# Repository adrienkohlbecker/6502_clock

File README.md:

# 6502 clock

## Board

## Schematic

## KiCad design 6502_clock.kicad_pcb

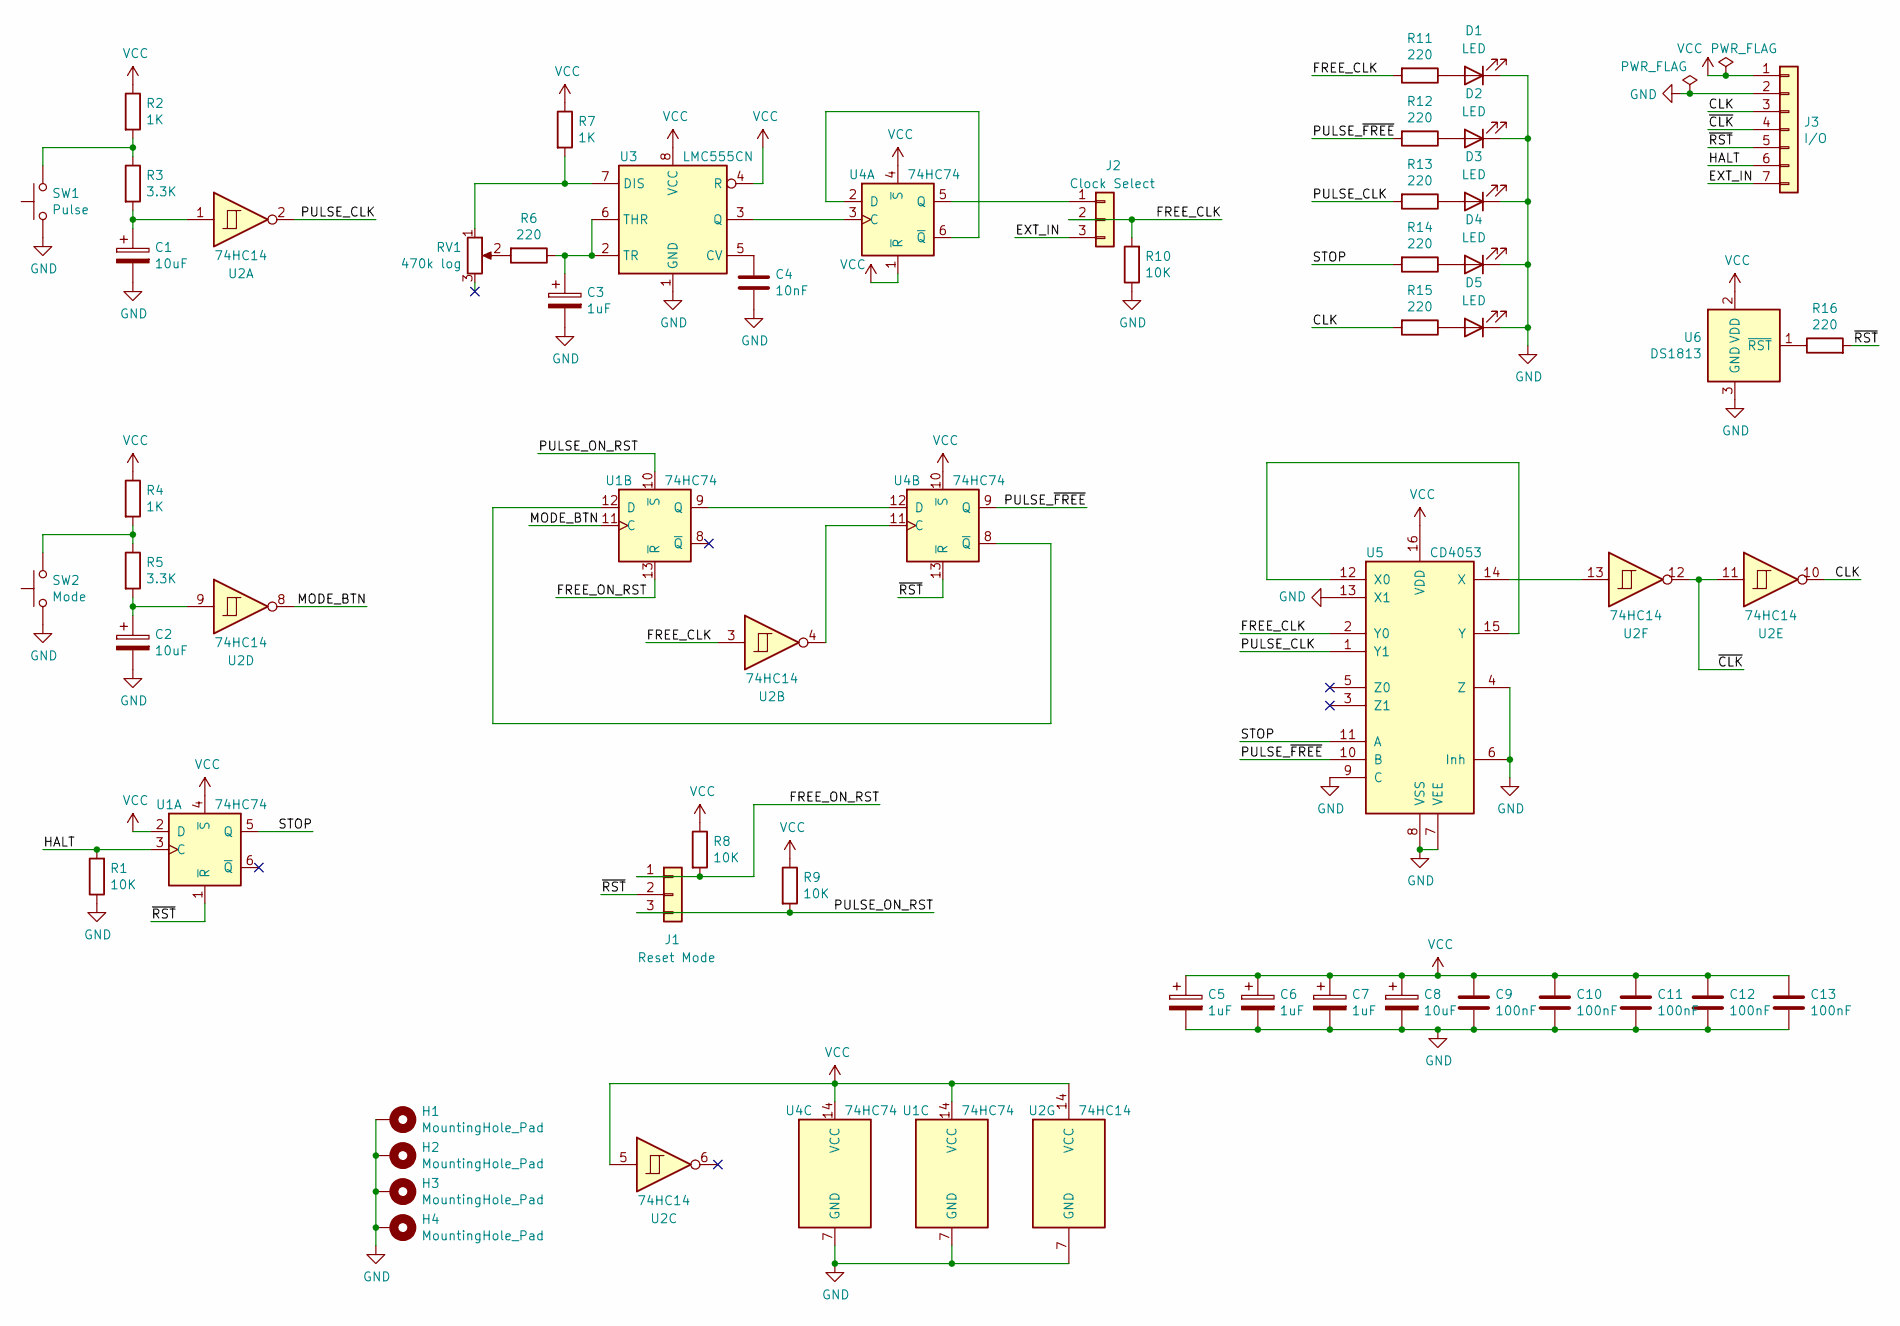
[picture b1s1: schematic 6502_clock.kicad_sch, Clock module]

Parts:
C1, C2, C8: 10uF; CP_Radial_D4.0mm_P2.00mm
C3, C5, C6, C7: 1uF; CP_Radial_D4.0mm_P2.00mm
C4: 10nF; C_Disc_D6.0mm_W2.5mm_P5.00mm
C9, C10, C11, C12, C13: 100nF; C_Disc_D5.0mm_W2.5mm_P2.50mm
D1, D2, D3, D4, D5: LED; LED_D3.0mm
H1, H2, H3, H4: MountingHole_Pad; MountingHole_3.2mm_M3_Pad
J1: Reset Mode; PinSocket_1x03_P2.54mm_Vertical
J2: Clock Select; PinSocket_1x03_P2.54mm_Vertical
J3: I/O; PinSocket_1x07_P2.54mm_Vertical
R1, R8, R9, R10: 10K; R_Axial_DIN0207_L6.3mm_D2.5mm_P7.62mm_Horizontal
R2, R4, R7: 1K; R_Axial_DIN0207_L6.3mm_D2.5mm_P7.62mm_Horizontal
R3, R5: 3.3K; R_Axial_DIN0207_L6.3mm_D2.5mm_P7.62mm_Horizontal
R6, R11, R12, R13, R14, R15, R16: 220; R_Axial_DIN0207_L6.3mm_D2.5mm_P7.62mm_Horizontal
RV1: 470k log; Potentiometer_P160KN-0QC15C500K
SW1: Pulse; SW_PUSH_6mm
SW2: Mode; SW_PUSH_6mm
U1, U4: 74HC74; DIP-14_W7.62mm
U2: 74HC14; DIP-14_W7.62mm
U3: LMC555CN; DIP-8_W7.62mm
U5: CD4053; DIP-16_W7.62mm
U6: DS1813; TO-92_Inline

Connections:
CLK: J3.3, R15.2, U2.10
EXT_IN: J2.3, J3.7
FREE_CLK: J2.2, R10.2, R11.2, U2.3, U5.2 (Y0)
FREE_ON_RST: J1.1, R8.2, U1.13 (~R)
GND: C1.2, C2.2, C3.2, C4.1, C5.2, C6.2, C7.2, C8.2, C9.1, C10.1, C11.1, C12.1, C13.1, D1.1 (K), D2.1 (K), D3.1 (K), D4.1 (K), D5.1 (K), H1.1, H2.1, H3.1, H4.1, J3.2, R1.1, R10.1, SW1.1, SW2.1, U1.7 (GND), U2.7 (GND), U3.1 (GND), U4.7 (GND), U5.4 (Z), U5.6 (Inh), U5.7 (VEE), U5.8 (VSS), U5.9 (C), U5.13 (X1), U6.3 (GND)
HALT: J3.6, R1.2, U1.3 (C)
MODE_BTN: U1.11 (C), U2.8
unnamed: C1.1, R3.2, U2.1
unnamed: C2.1, R5.2, U2.9
unnamed: C3.1, R6.1, U3.2 (TR), U3.6 (THR)
unnamed: C4.2, U3.5 (CV)
unnamed: D1.2 (A), R11.1
unnamed: D2.2 (A), R12.1
unnamed: D3.2 (A), R13.1
unnamed: D4.2 (A), R14.1
unnamed: D5.2 (A), R15.1
unnamed: J2.1, U4.5 (Q)
unnamed: R2.2, R3.1, SW1.2
unnamed: R4.2, R5.1, SW2.2
unnamed: R6.2, RV1.2
unnamed: R7.2, RV1.1, U3.7 (DIS)
unnamed: R16.1, U6.1 (~RST)
unnamed: U1.9 (Q), U4.12 (D)
unnamed: U1.12 (D), U4.8 (~Q)
unnamed: U2.4, U4.11 (C)
unnamed: U2.13, U5.14 (X)
unnamed: U3.3 (Q), U4.3 (C)
unnamed: U4.2 (D), U4.6 (~Q)
unnamed: U5.12 (X0), U5.15 (Y)
PULSE_CLK: R13.2, U2.2, U5.1 (Y1)
PULSE_ON_RST: J1.3, R9.2, U1.10 (~S)
PULSE_~FREE: R12.2, U4.9 (Q), U5.10 (B)
STOP: R14.2, U1.5 (Q), U5.11 (A)
VCC: C5.1, C6.1, C7.1, C8.1, C9.2, C10.2, C11.2, C12.2, C13.2, J3.1, R2.1, R4.1, R7.1, R8.1, R9.1, U1.2 (D), U1.4 (~S), U1.14 (VCC), U2.5, U2.14 (VCC), U3.4 (R), U3.8 (VCC), U4.1 (~R), U4.4 (~S), U4.10 (~S), U4.14 (VCC), U5.16 (VDD), U6.2 (VDD)
~CLK: J3.4, U2.11, U2.12
~RST: J1.2, J3.5, R16.2, U1.1 (~R), U4.13 (~R)

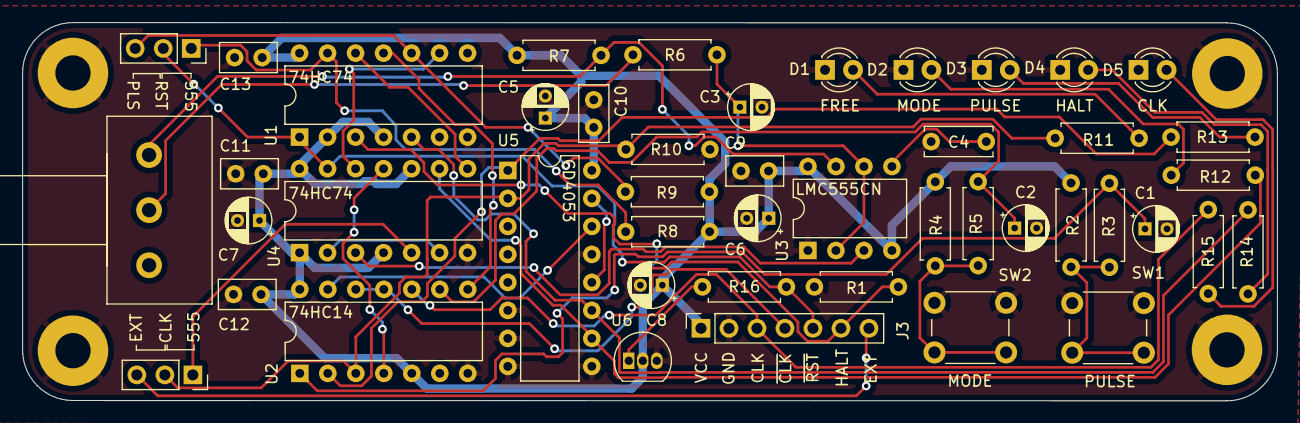
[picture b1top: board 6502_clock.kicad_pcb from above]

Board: 2 copper layers, 113.9 x 34.3 mm, 50 parts (0 on the bottom side), 36 nets.

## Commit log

2021-05-30 Add clock
2021-07-13 Update clock
2021-08-04 Fixed clock
2021-11-19 Fix component values
2021-12-19 Remove ignored files
2023-06-06 Update for KiCad 6
